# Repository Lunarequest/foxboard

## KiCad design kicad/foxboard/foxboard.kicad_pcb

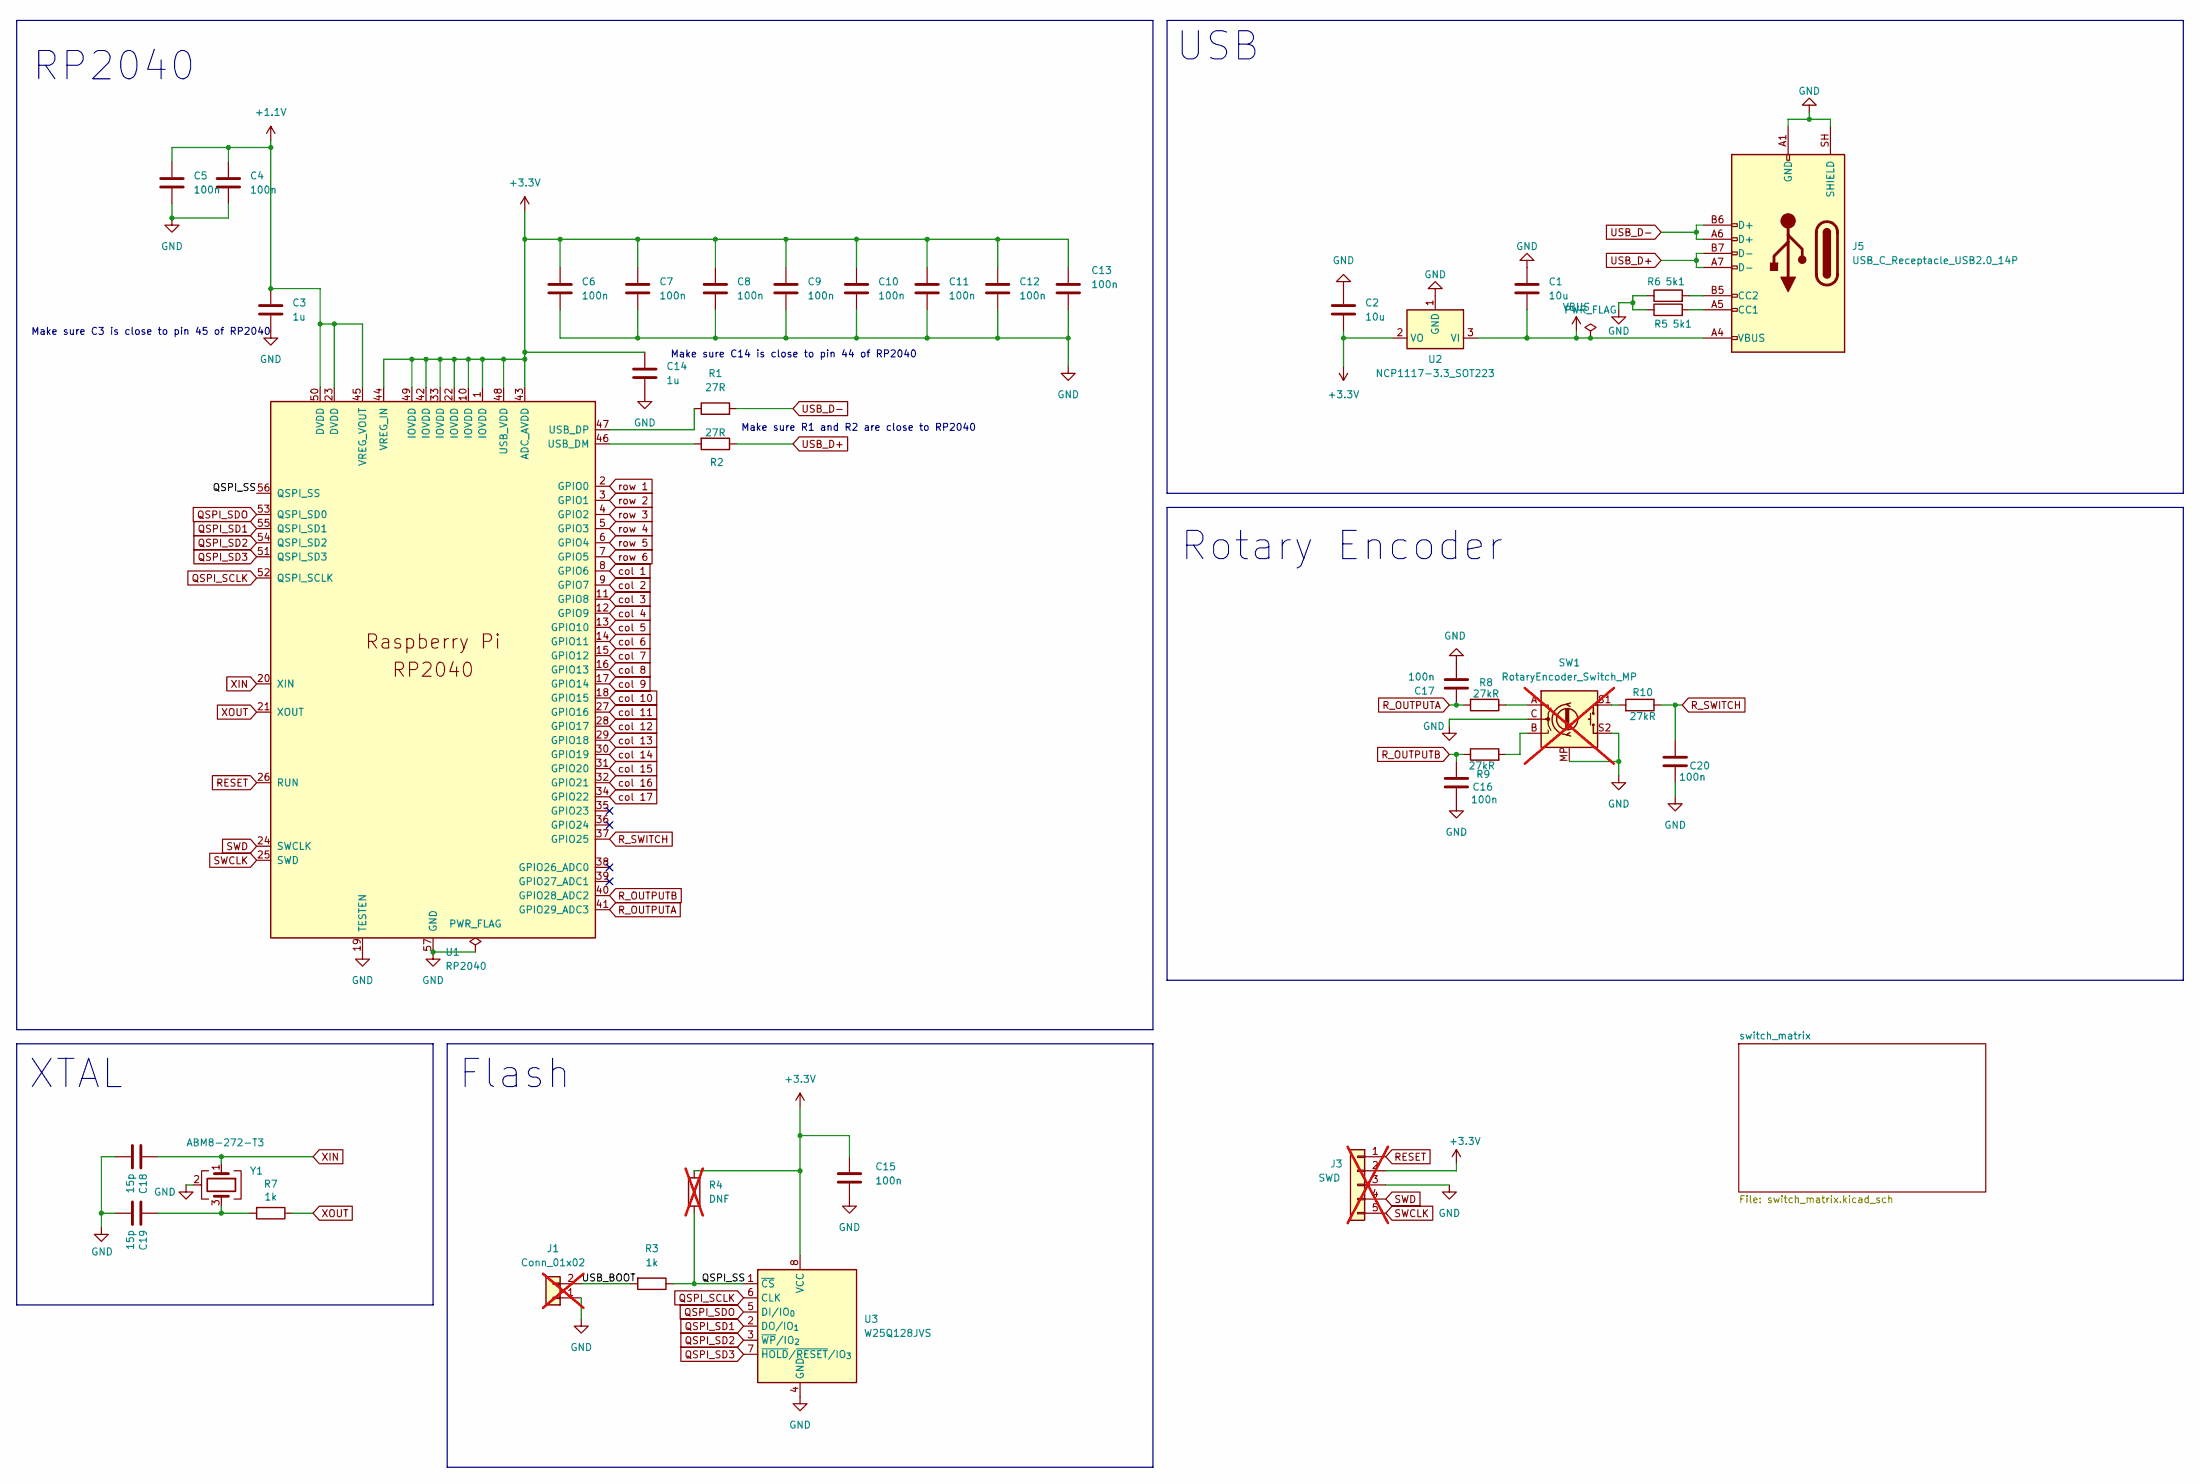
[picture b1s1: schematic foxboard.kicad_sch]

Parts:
C1, C2: 10u; C_0402_1005Metric_Pad0.74x0.62mm_HandSolder; MPN CL05A106MP5NUNC; LCSC C315248
C3, C14: 1u; C_0402_1005Metric_Pad0.74x0.62mm_HandSolder; MPN CL05A105KO5NNNC; LCSC C29266
C4, C5, C6, C7, C8, C9, C10, C11, C12, C13, C15, C16, C17, C20: 100n; C_0402_1005Metric_Pad0.74x0.62mm_HandSolder; MPN CL05B104KP5VPNC; LCSC C16193311
C18, C19: 15p; C_0402_1005Metric; MPN CL05C150JB5NNNC; LCSC C86285
J1: Conn_01x02; PinHeader_1x02_P2.54mm_Vertical; not fitted
J3: SWD; PinSocket_1x05_P2.54mm_Vertical; not fitted
J5: USB_C_Receptacle_USB2.0_14P; USB_C_Receptacle_HRO_TYPE-C-31-M-12; MPN TYPE-C-31-M-12; LCSC C165948
R1, R2: 27R; R_0402_1005Metric_Pad0.72x0.64mm_HandSolder; MPN 0402WGF1001TCE; LCSC C11702
R3, R7: 1k; R_0402_1005Metric_Pad0.72x0.64mm_HandSolder; MPN UNI-ROYAL TC0225B1001TCC; LCSC C2989674
R4: DNF; R_0402_1005Metric_Pad0.72x0.64mm_HandSolder; not fitted
R5, R6: 5k1; R_0402_1005Metric_Pad0.72x0.64mm_HandSolder; MPN 0402WGF5101TCE; LCSC C25905
R8, R9, R10: 27kR; R_0402_1005Metric_Pad0.72x0.64mm_HandSolder; MPN CRCW040227R0JNED
SW1: RotaryEncoder_Switch_MP; RotaryEncoder_Bourns_Horizontal_PEC12R-2x17F-Sxxxx; not fitted
U1: RP2040; RP2040-QFN-56; MPN RP2040; LCSC C2040
U2: NCP1117-3.3_SOT223; SOT-223-3_TabPin2; MPN NCP1117STAT3G; LCSC C20546
U3: W25Q128JVS; SOIC-8_5.3x5.3mm_P1.27mm; MPN W25Q128JVSIQ; LCSC C97521
Y1: ABM8-272-T3; Crystal_SMD_3225-4Pin_3.2x2.5mm; MPN XC32M4-12.000-F10NNFT; LCSC C2842186

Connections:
+1.1V: C3.1, C4.1, C5.1, U1.23 (DVDD), U1.45 (VREG_VOUT), U1.50 (DVDD)
+3.3V: C2.2, C6.1, C7.1, C8.1, C9.1, C10.1, C11.1, C12.1, C13.1, C14.1, C15.1, J3.2, R4.1, U1.1 (IOVDD), U1.10 (IOVDD), U1.22 (IOVDD), U1.33 (IOVDD), U1.42 (IOVDD), U1.43 (ADC_AVDD), U1.44 (VREG_IN), U1.48 (USB_VDD), U1.49 (IOVDD), U2.2 (VO), U3.8 (VCC)
/QSPI_SS: R3.1, R4.2, U1.56 (QSPI_SS), U3.1 (~CS)
/USB_BOOT: J1.2, R3.2
GND: C1.2, C2.1, C3.2, C4.2, C5.2, C6.2, C7.2, C8.2, C9.2, C10.2, C11.2, C12.2, C13.2, C14.2, C15.2, C16.2, C17.2, C18.2, C19.2, C20.2, J1.1, J3.3, J5.A1 (GND), J5.A12 (GND), J5.B1 (GND), J5.B12 (GND), J5.SH (SHIELD), R5.1, R6.1, SW1.C, SW1.MP, SW1.S2, U1.19 (TESTEN), U1.57 (GND), U2.1 (GND), U3.4 (GND), Y1.2 (G), Y1.4 (G)
unnamed: C19.1, R7.2, Y1.3
unnamed: J5.A5 (CC1), R5.2
unnamed: J5.B5 (CC2), R6.2
unnamed: R8.1, SW1.A
unnamed: R9.2, SW1.B
unnamed: R10.2, SW1.S1
unnamed: R2.2, U1.46 (USB_DM)
unnamed: R1.1, U1.47 (USB_DP)
QSPI_SCLK: U1.52 (QSPI_SCLK), U3.6 (CLK)
QSPI_SD1: U1.55 (QSPI_SD1), U3.2 (DO/IO_{1})
QSPI_SD2: U1.54 (QSPI_SD2), U3.3 (~WP/IO_{2})
QSPI_SD3: U1.51 (QSPI_SD3), U3.7 (~HOLD/~RESET/IO_{3})
QSPI_SDO: U1.53 (QSPI_SD0), U3.5 (DI/IO_{0})
RESET: J3.1, U1.26 (RUN)
R_OUTPUTA: C17.1, R8.2, U1.41 (GPIO29_ADC3)
R_OUTPUTB: C16.1, R9.1, U1.40 (GPIO28_ADC2)
R_SWITCH: C20.1, R10.1, U1.37 (GPIO25)
SWCLK: J3.5, U1.25 (SWD)
SWD: J3.4, U1.24 (SWCLK)
USB_D+: J5.A7 (D-), J5.B7 (D-), R2.1
USB_D-: J5.A6 (D+), J5.B6 (D+), R1.2
VBUS: C1.1, J5.A4 (VBUS), J5.A9 (VBUS), J5.B4 (VBUS), J5.B9 (VBUS), U2.3 (VI)
XIN: C18.1, U1.20 (XIN), Y1.1
XOUT: R7.1, U1.21 (XOUT)
col 1: U1.8 (GPIO6); also elsewhere on the board
col 2: U1.9 (GPIO7); also elsewhere on the board
col 3: U1.11 (GPIO8); also elsewhere on the board
col 4: U1.12 (GPIO9); also elsewhere on the board
col 5: U1.13 (GPIO10); also elsewhere on the board
col 6: U1.14 (GPIO11); also elsewhere on the board
col 7: U1.15 (GPIO12); also elsewhere on the board
col 8: U1.16 (GPIO13); also elsewhere on the board
col 9: U1.17 (GPIO14); also elsewhere on the board
col 10: U1.18 (GPIO15); also elsewhere on the board
col 11: U1.27 (GPIO16); also elsewhere on the board
col 12: U1.28 (GPIO17); also elsewhere on the board
col 13: U1.29 (GPIO18); also elsewhere on the board
col 14: U1.30 (GPIO19); also elsewhere on the board
col 15: U1.31 (GPIO20); also elsewhere on the board
col 16: U1.32 (GPIO21); also elsewhere on the board
col 17: U1.34 (GPIO22); also elsewhere on the board
row 1: U1.2 (GPIO0); also elsewhere on the board
row 2: U1.3 (GPIO1); also elsewhere on the board
row 3: U1.4 (GPIO2); also elsewhere on the board
row 4: U1.5 (GPIO3); also elsewhere on the board
row 5: U1.6 (GPIO4); also elsewhere on the board
row 6: U1.7 (GPIO5); also elsewhere on the board

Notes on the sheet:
USB
RP2040
Make sure C14 is close to pin 44 of RP2040
XTAL
Rotary Encoder
Make sure C3 is close to pin 45 of RP2040
Make sure R1 and R2 are close to RP2040
Flash

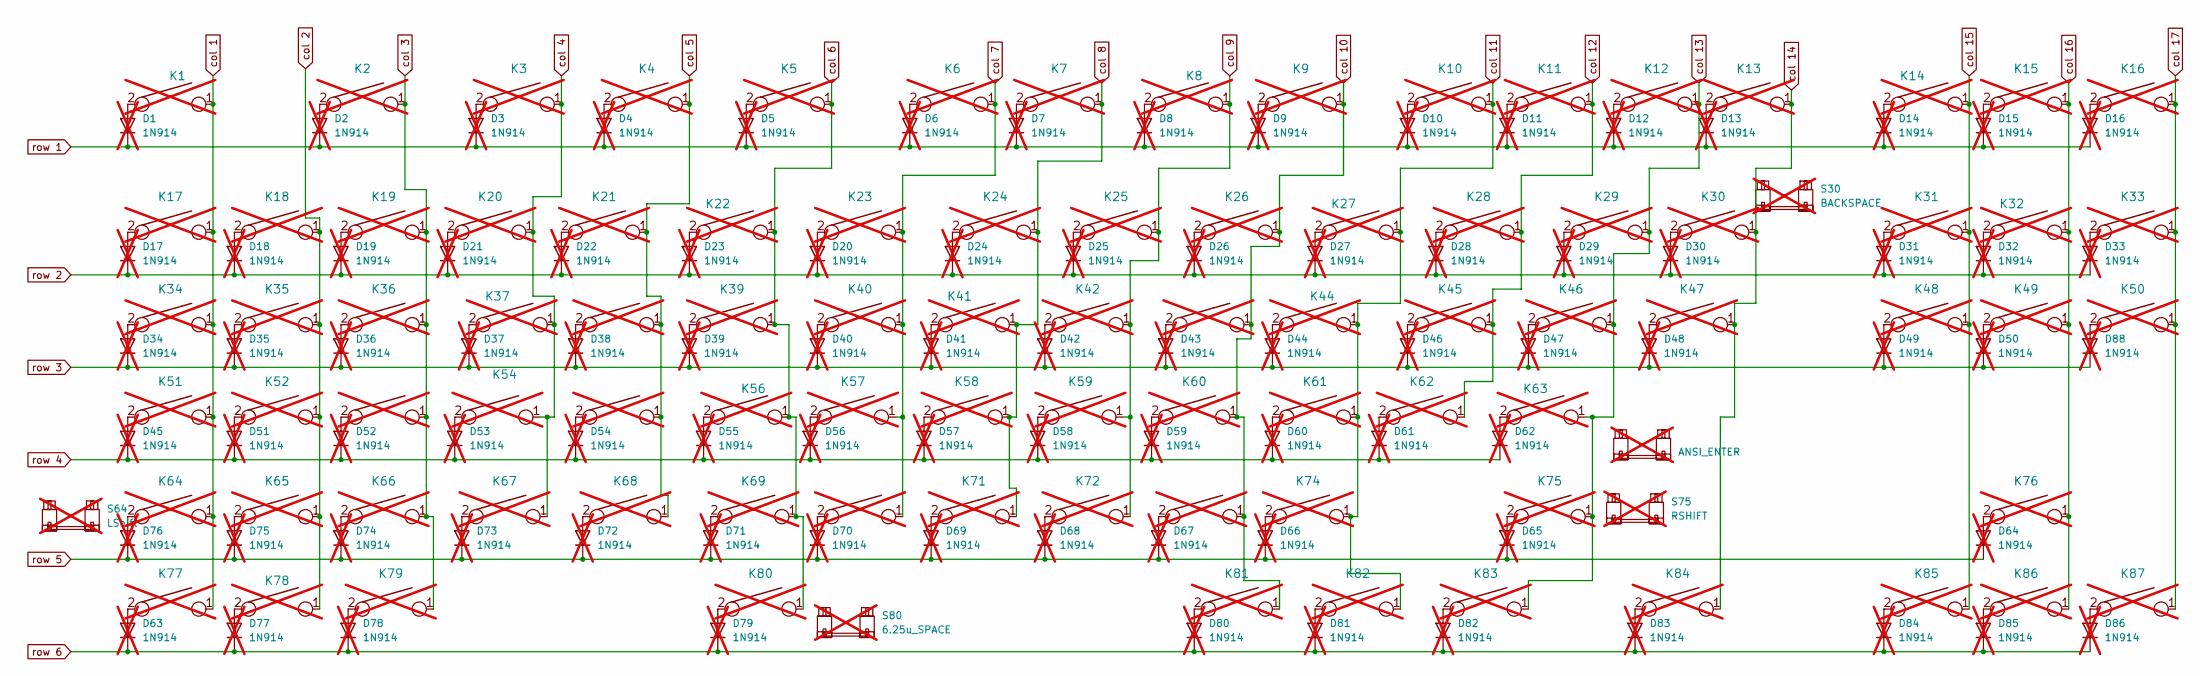
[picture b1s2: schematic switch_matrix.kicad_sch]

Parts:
D1, D2, D3, D4, D5, D6, D7, D8, D9, D10, D11, D12, D13, D14, D15, D16, D17, D18, D19, D20, D21, D22, D23, D24, D25, D26, D27, D28, D29, D30, D31, D32, D33, D34, D35, D36, D37, D38, D39, D40, D41, D42, D43, D44, D45, D46, D47, D48, D49, D50, D51, D52, D53, D54, D55, D56, D57, D58, D59, D60, D61, D62, D63, D64, D65, D66, D67, D68, D69, D70, D71, D72, D73, D74, D75, D76, D77, D78, D79, D80, D81, D82, D83, D84, D85, D86, D88: 1N914; D_DO-35_SOD27_P7.62mm_Horizontal; MPN 1N914TAP; LCSC C17693320; not fitted
K1, K2, K3, K4, K5, K6, K7, K8, K10, K11, K12, K13, K14, K16, K17, K18, K19, K20, K21, K22, K23, K24, K25, K26, K27, K28, K29, K30, K31, K32, K33, K35, K36, K37, K38, K39, K40, K41, K42, K43, K44, K45, K46, K48, K49, K50, K52, K53, K54, K55, K56, K57, K58, K59, K60, K61, K62, K63, K64, K65, K66, K67, K68, K69, K70, K71, K72, K73, K74, K75, K76, K80, K84, K85, K86, K87: KEYSW; SW_MX_1u; not fitted
K9, K15, K77, K78, K79, K81, K82, K83: KEYSW; SW_MX_1.25u; not fitted
K34, K47: KEYSW; SW_MX_1.5u; not fitted
K51: KEYSW; SW_MX_1.75u; not fitted
S30: BACKSPACE; STAB_MX_2u; not fitted
S63: ANSI_ENTER; STAB_MX_2.25u; not fitted
S64: LShift; STAB_MX_2.25u; not fitted
S75: RSHIFT; STAB_MX_P_2.75u; not fitted
S80: 6.25u_SPACE; STAB_MX_P_6.25u; not fitted

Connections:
unnamed: D1.2 (A), K1.2
unnamed: D2.2 (A), K2.2
unnamed: D3.2 (A), K3.2
unnamed: D4.2 (A), K4.2
unnamed: D5.2 (A), K5.2
unnamed: D6.2 (A), K6.2
unnamed: D7.2 (A), K7.2
unnamed: D8.2 (A), K8.2
unnamed: D9.2 (A), K9.2
unnamed: D10.2 (A), K10.2
unnamed: D11.2 (A), K11.2
unnamed: D12.2 (A), K12.2
unnamed: D13.2 (A), K13.2
unnamed: D14.2 (A), K14.2
unnamed: D15.2 (A), K15.2
unnamed: D16.2 (A), K16.2
unnamed: D17.2 (A), K17.2
unnamed: D18.2 (A), K18.2
unnamed: D19.2 (A), K19.2
unnamed: D20.2 (A), K23.2
unnamed: D21.2 (A), K20.2
unnamed: D22.2 (A), K21.2
unnamed: D23.2 (A), K22.2
unnamed: D24.2 (A), K24.2
unnamed: D25.2 (A), K25.2
unnamed: D26.2 (A), K26.2
unnamed: D27.2 (A), K27.2
unnamed: D28.2 (A), K28.2
unnamed: D29.2 (A), K29.2
unnamed: D30.2 (A), K30.2
unnamed: D31.2 (A), K31.2
unnamed: D32.2 (A), K32.2
unnamed: D33.2 (A), K33.2
unnamed: D34.2 (A), K34.2
unnamed: D35.2 (A), K35.2
unnamed: D36.2 (A), K36.2
unnamed: D37.2 (A), K37.2
unnamed: D38.2 (A), K38.2
unnamed: D39.2 (A), K39.2
unnamed: D40.2 (A), K40.2
unnamed: D41.2 (A), K41.2
unnamed: D42.2 (A), K42.2
unnamed: D43.2 (A), K43.2
unnamed: D44.2 (A), K44.2
unnamed: D45.2 (A), K51.2
unnamed: D46.2 (A), K45.2
unnamed: D47.2 (A), K46.2
unnamed: D48.2 (A), K47.2
unnamed: D49.2 (A), K48.2
unnamed: D50.2 (A), K49.2
unnamed: D51.2 (A), K52.2
unnamed: D52.2 (A), K53.2
unnamed: D53.2 (A), K54.2
unnamed: D54.2 (A), K55.2
unnamed: D55.2 (A), K56.2
unnamed: D56.2 (A), K57.2
unnamed: D57.2 (A), K58.2
unnamed: D58.2 (A), K59.2
unnamed: D59.2 (A), K60.2
unnamed: D60.2 (A), K61.2
unnamed: D61.2 (A), K62.2
unnamed: D62.2 (A), K63.2
unnamed: D63.2 (A), K77.2
unnamed: D64.2 (A), K76.2
unnamed: D65.2 (A), K75.2
unnamed: D66.2 (A), K74.2
unnamed: D67.2 (A), K73.2
unnamed: D68.2 (A), K72.2
unnamed: D69.2 (A), K71.2
unnamed: D70.2 (A), K70.2
unnamed: D71.2 (A), K69.2
unnamed: D72.2 (A), K68.2
unnamed: D73.2 (A), K67.2
unnamed: D74.2 (A), K66.2
unnamed: D75.2 (A), K65.2
unnamed: D76.2 (A), K64.2
unnamed: D77.2 (A), K78.2
unnamed: D78.2 (A), K79.2
unnamed: D79.2 (A), K80.2
unnamed: D80.2 (A), K81.2
unnamed: D81.2 (A), K82.2
unnamed: D82.2 (A), K83.2
unnamed: D83.2 (A), K84.2
unnamed: D84.2 (A), K85.2
unnamed: D85.2 (A), K86.2
unnamed: D86.2 (A), K87.2
unnamed: D88.2 (A), K50.2
col 1: K1.1, K17.1, K34.1, K51.1, K64.1, K77.1; also elsewhere on the board
col 2: K18.1, K35.1, K52.1, K65.1, K78.1; also elsewhere on the board
col 3: K2.1, K19.1, K36.1, K53.1, K66.1, K79.1; also elsewhere on the board
col 4: K3.1, K20.1, K37.1, K54.1, K67.1; also elsewhere on the board
col 5: K4.1, K21.1, K38.1, K55.1, K68.1; also elsewhere on the board
col 6: K5.1, K22.1, K39.1, K56.1, K69.1, K80.1; also elsewhere on the board
col 7: K6.1, K23.1, K40.1, K57.1, K70.1; also elsewhere on the board
col 8: K7.1, K24.1, K41.1, K58.1, K71.1; also elsewhere on the board
col 9: K8.1, K25.1, K42.1, K59.1, K72.1; also elsewhere on the board
col 10: K9.1, K26.1, K43.1, K60.1, K73.1, K81.1; also elsewhere on the board
col 11: K10.1, K27.1, K44.1, K61.1, K74.1, K82.1; also elsewhere on the board
col 12: K11.1, K28.1, K45.1, K62.1; also elsewhere on the board
col 13: K12.1, K29.1, K46.1, K63.1, K75.1, K83.1; also elsewhere on the board
col 14: K13.1, K30.1, K47.1, K84.1; also elsewhere on the board
col 15: K14.1, K31.1, K48.1, K85.1; also elsewhere on the board
col 16: K15.1, K32.1, K49.1, K76.1, K86.1; also elsewhere on the board
col 17: K16.1, K33.1, K50.1, K87.1; also elsewhere on the board
row 1: D1.1 (K), D2.1 (K), D3.1 (K), D4.1 (K), D5.1 (K), D6.1 (K), D7.1 (K), D8.1 (K), D9.1 (K), D10.1 (K), D11.1 (K), D12.1 (K), D13.1 (K), D14.1 (K), D15.1 (K), D16.1 (K); also elsewhere on the board
row 2: D17.1 (K), D18.1 (K), D19.1 (K), D20.1 (K), D21.1 (K), D22.1 (K), D23.1 (K), D24.1 (K), D25.1 (K), D26.1 (K), D27.1 (K), D28.1 (K), D29.1 (K), D30.1 (K), D31.1 (K), D32.1 (K), D33.1 (K); also elsewhere on the board
row 3: D34.1 (K), D35.1 (K), D36.1 (K), D37.1 (K), D38.1 (K), D39.1 (K), D40.1 (K), D41.1 (K), D42.1 (K), D43.1 (K), D44.1 (K), D46.1 (K), D47.1 (K), D48.1 (K), D49.1 (K), D50.1 (K), D88.1 (K); also elsewhere on the board
row 4: D45.1 (K), D51.1 (K), D52.1 (K), D53.1 (K), D54.1 (K), D55.1 (K), D56.1 (K), D57.1 (K), D58.1 (K), D59.1 (K), D60.1 (K), D61.1 (K), D62.1 (K); also elsewhere on the board
row 5: D64.1 (K), D65.1 (K), D66.1 (K), D67.1 (K), D68.1 (K), D69.1 (K), D70.1 (K), D71.1 (K), D72.1 (K), D73.1 (K), D74.1 (K), D75.1 (K), D76.1 (K); also elsewhere on the board
row 6: D63.1 (K), D77.1 (K), D78.1 (K), D79.1 (K), D80.1 (K), D81.1 (K), D82.1 (K), D83.1 (K), D84.1 (K), D85.1 (K), D86.1 (K); also elsewhere on the board

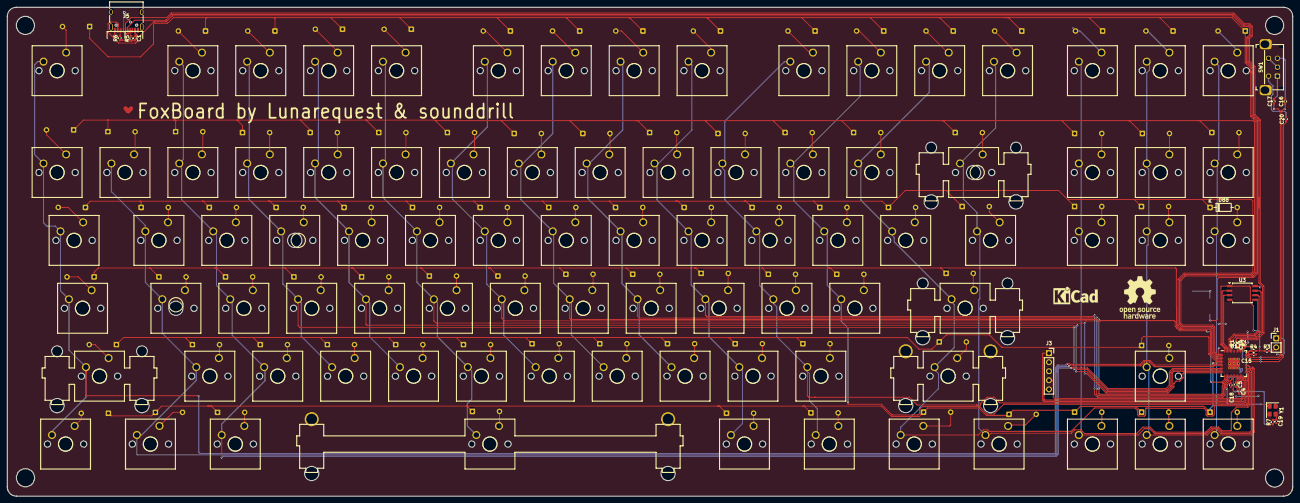
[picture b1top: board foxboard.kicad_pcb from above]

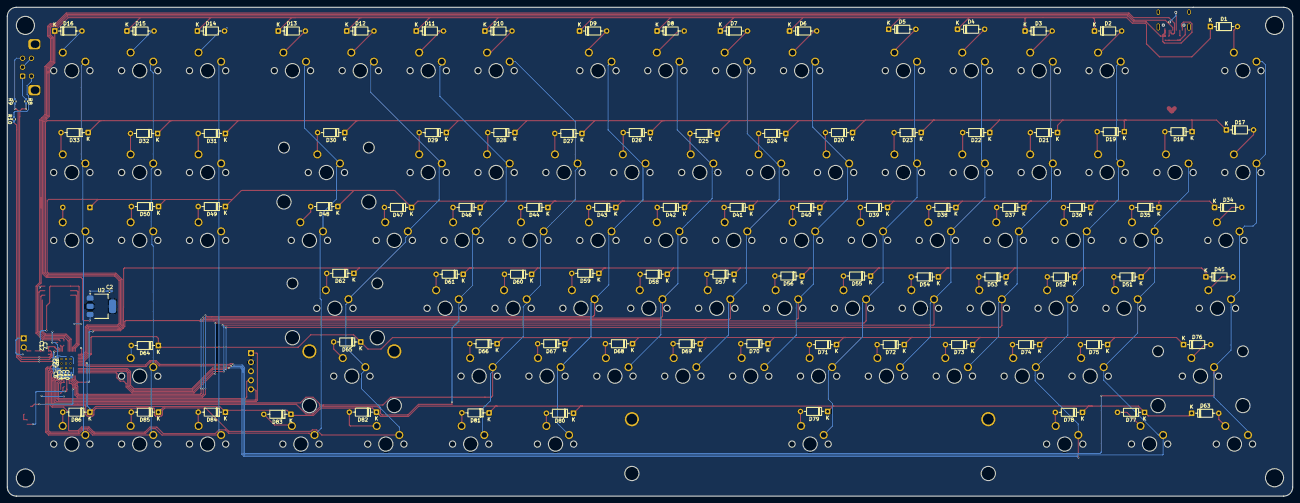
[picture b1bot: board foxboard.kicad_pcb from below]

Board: 2 copper layers, 360.7 x 137.2 mm, 217 parts (99 on the bottom side), 139 nets.

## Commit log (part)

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2023-06-28 wip foxboard
2024-01-16 move teensy and stuff
2024-01-16 add keyswitch and change some footprints
2024-01-16 update layout
2024-01-16 update some footprints and move most diodes into place
2024-01-16 update footprints
2024-01-16 finish layout
2024-01-17 move all resitors, caps and diodes to the back of the pcb
2024-01-17 move a keyswitch
2024-01-17 flip diode that was missing
2024-01-17 reimported keyboard-layout.dxf as Foreground Silk Layer
2024-01-18 add rows
2024-01-19 add few rows update eeschema
2024-01-19 add few cols & update eeschema
2024-01-19 add finish cols and usbc & update eeschema
2024-01-19 Cleaned up the USB-C connector layout and made use of power symbols for schematic clarity
2024-01-19 Made the footprint libraries project-relative
2024-01-19 move teensy a little back
2024-01-20 hook up resistor to ground
2024-01-21 switch to better layout
2024-01-21 use usbc 2.0 recepticale
2024-01-21 add fill
2024-01-22 add hardware license and skeleton of firmware
2024-01-24 add footprint for SOD882D & RESC168X55N
2024-06-09 update deps
2024-06-11 make sure all connections are connected, change resistor package to 0805
2024-08-19 update firmware
2026-05-15 wip v2
2026-05-15 fix most violations
2026-05-15 drop lck file
2026-05-16 add powerflags
2026-05-16 fix all warnings
2026-05-16 assigned footprints
2026-05-18 finish matrix
2026-05-24 Finish routing pcb
2026-05-27 fabrication outputs
2026-05-28 Include rotary encoder and cleanup some wires
2026-05-28 Close kicad(cleans up some lock files)
2026-06-05 chore: moved the switch matrix into another sheet
2026-06-05 chore: neatly ordered sections of schematic into named blocks
2026-06-05 chore: updated gitignore with files not needed in git
